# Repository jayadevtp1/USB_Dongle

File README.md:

# USB_Dongle
# PCB Design
started with edgecuts.then place all the components .Then enter into the most time consuming part the pcb rooting.it take me much time.
there occur so many drs connections. then recheck and completed the rooting .All the suffes finished.

# Schematic for the USB_Dongle
started with finding a best microcontroller for this project in online. After some research found out that esp32 is best. 
Then started started cooking. At first findout the essential components and schematic layout of it. Then started cooking schematic diagram in kicad. 
here the schematic that i created.i look ugle that i am not sorted every thing. Then i stoped my work for some time.

**Total time spent: 12h**

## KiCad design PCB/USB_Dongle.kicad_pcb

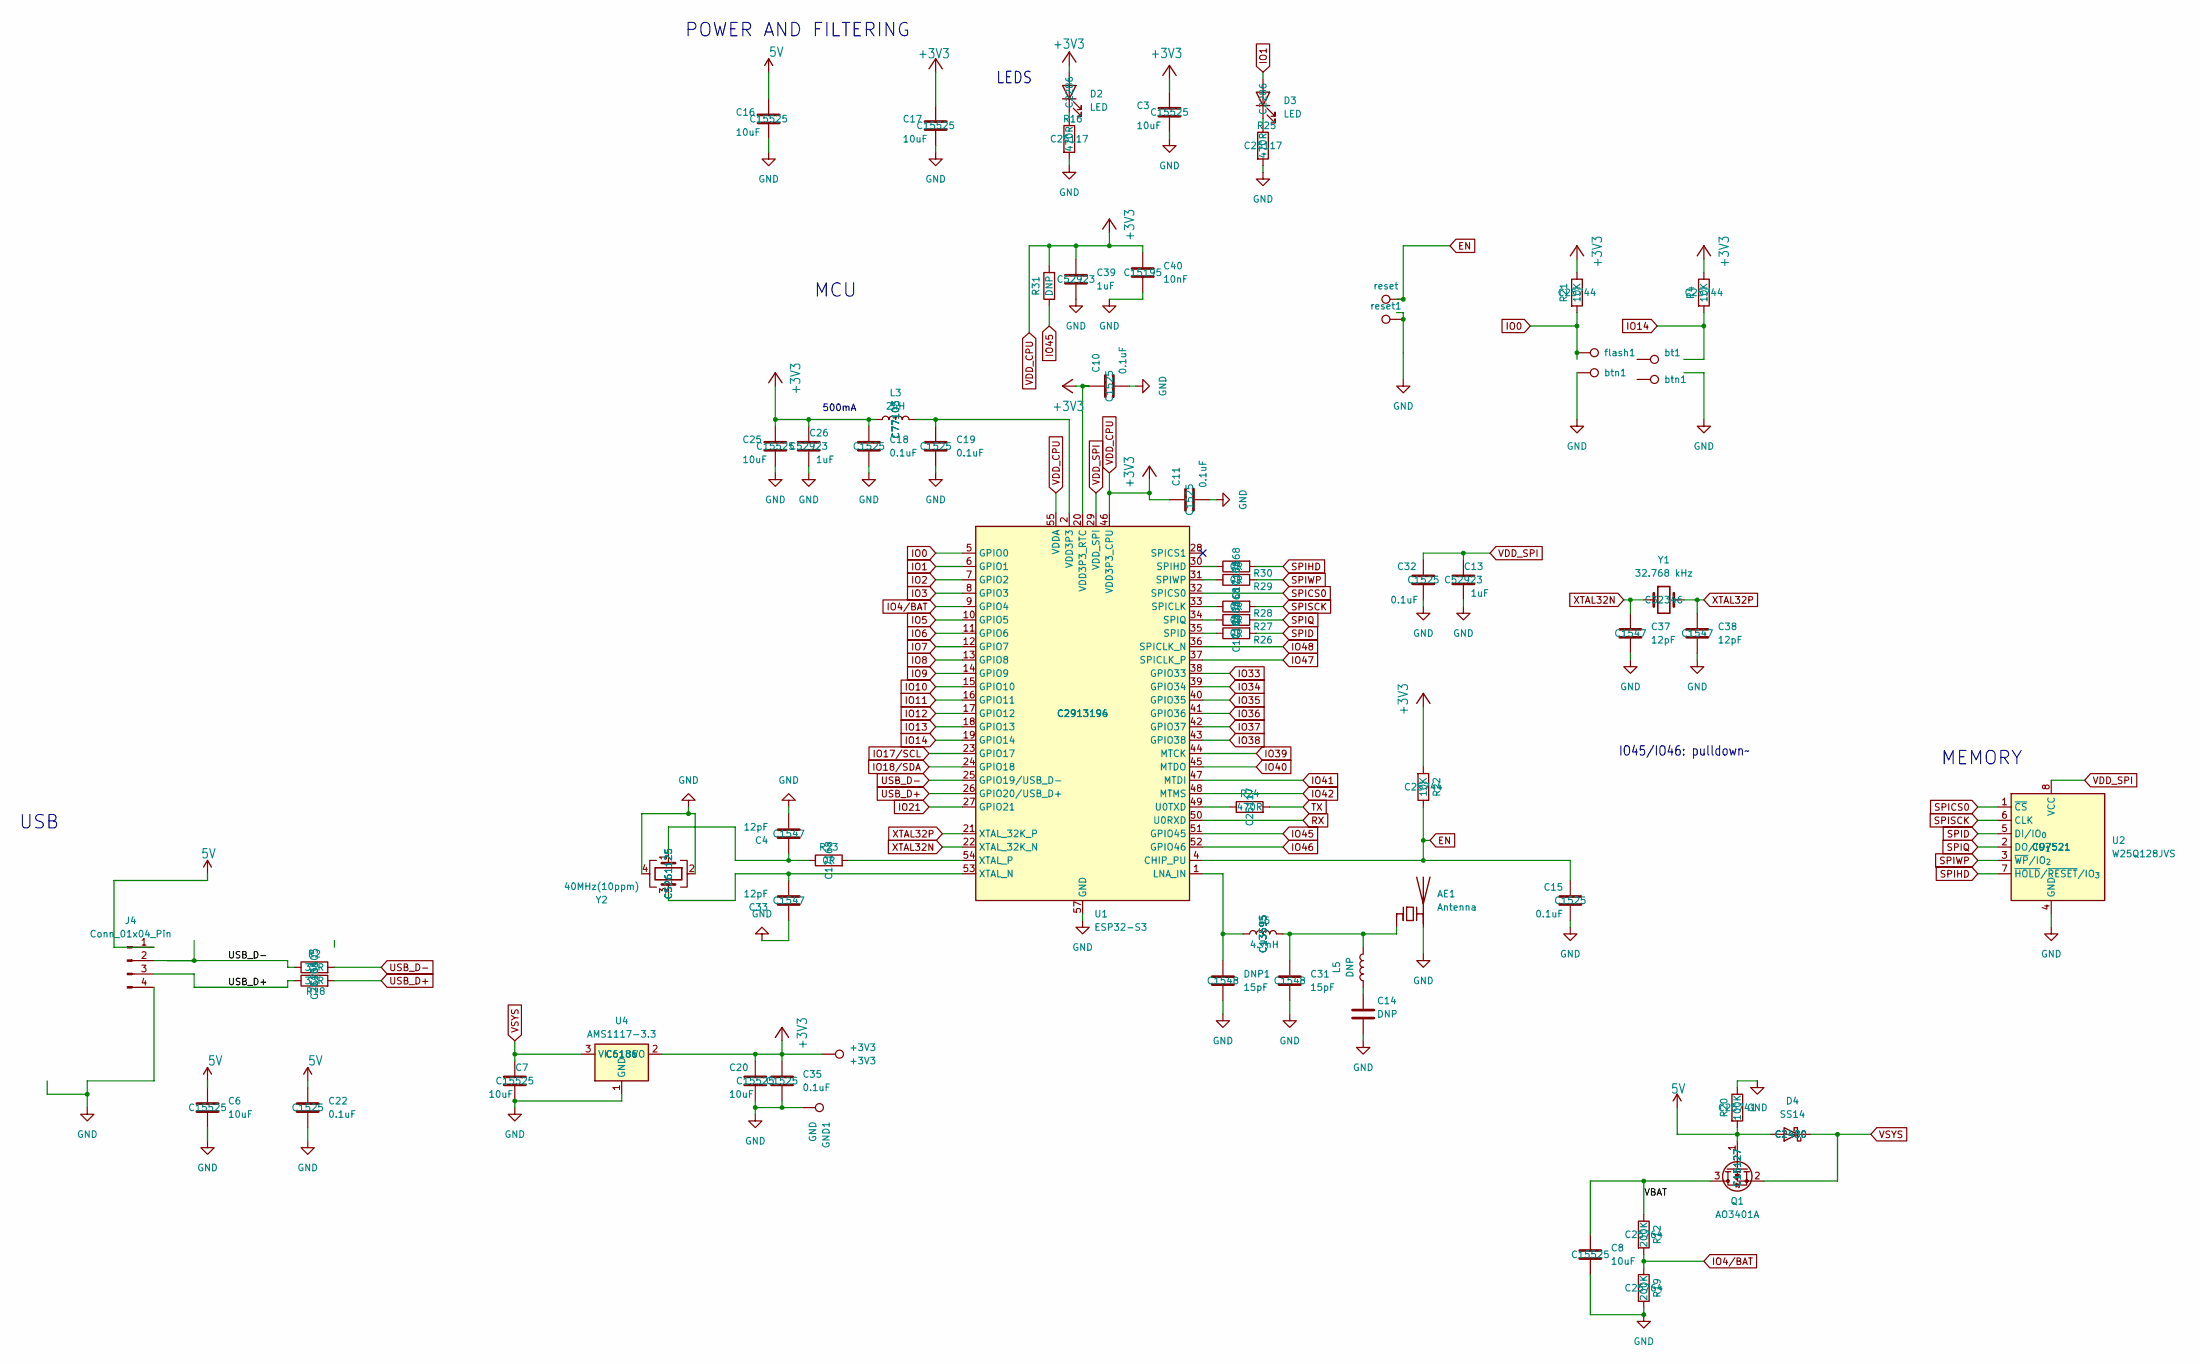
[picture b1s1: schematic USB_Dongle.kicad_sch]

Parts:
+3V1, +3V2: btn1; TestPoint_Pad_D1.0mm
+3V3: +3V3; TestPoint_Pad_D1.0mm
+3V4: reset; TestPoint_Pad_D1.0mm
AE1: Antenna; Texas_SWRA117D_2.4GHz_Left
C3, C6, C7, C8, C16, C17, C20, C25: 10uF; C_0402_1005Metric; MNF PART NUMBER C15525; LCSC C15525
C4, C33, C37, C38: 12pF; C_0402_1005Metric; MNF PART NUMBER C1547; LCSC C1547
C10, C11, C15, C18, C19, C22, C32, C35: 0.1uF; C_0402_1005Metric; MNF PART NUMBER C1525; LCSC C1525
C13, C26, C39: 1uF; C_0402_1005Metric; MNF PART NUMBER C52923; LCSC C52923
C14: DNP; C_0402_1005Metric
C31: 15pF; C_0402_1005Metric; MNF PART NUMBER C1548; LCSC C1548
C40: 10nF; C_0402_1005Metric; MNF PART NUMBER C15195; LCSC C15195
D2, D3: LED; LED_0603_1608Metric; MNF PART NUMBER C2286; LCSC C2286
D4: SS14; D_SMA; MNF PART NUMBER C2480; LCSC C2480
DNP1: 15pF; C_0402_1005Metric; MNF PART NUMBER C1548; LCSC C1548
GND1: GND; TestPoint_Pad_D1.0mm
J4: Conn_01x04_Pin; USB_A_PCB_Edge_receptacle
L3: 2nH; L_0402_1005Metric; MNF PART NUMBER C77103; LCSC C77103
L5: DNP; L_0402_1005Metric
L6: 4.7nH; L_0402_1005Metric; MNF PART NUMBER C13595; LCSC C13595
Q1: AO3401A; SOT-23; MNF PART NUMBER C15127; LCSC C15127
R2, R18: 33R; R_0402_1005Metric; MNF PART NUMBER C25105; LCSC C25105
R4, R21, R22: 10K; R_0402_1005Metric; MNF PART NUMBER C25744; LCSC C25744
R12, R19: 200K; R_0402_1005Metric; MNF PART NUMBER C25764; LCSC C25764
R16, R24, R25: 470R; R_0402_1005Metric; MNF PART NUMBER C25117; LCSC C25117
R20: 100K; R_0402_1005Metric; MNF PART NUMBER C25741; LCSC C25741
R23, R26, R27, R28, R29, R30: 0R; R_0402_1005Metric; MNF PART NUMBER C17168; LCSC C17168
R31: DNP; R_0402_1005Metric
U1: ESP32-S3; QFN-56-1EP_7x7mm_P0.4mm_EP4x4mm; MNF PART NUMBER C2913196; LCSC C2913194
U2: W25Q128JVS; SOIC-8_5.23x5.23mm_P1.27mm; MNF PART NUMBER C97521; LCSC C97521
U4: AMS1117-3.3; SOT-223-3_TabPin2; MNF PART NUMBER C6186; LCSC C6186
Y1: 32.768 kHz; Crystal_SMD_3215-2Pin_3.2x1.5mm; MNF PART NUMBER C32346; LCSC C32346
Y2: 40MHz(10ppm); Crystal_SMD_2520-4Pin_2.5x2.0mm; MNF PART NUMBER C5261125; LCSC C5261125
bt1: +3V3; TestPoint_Pad_D1.0mm
flash1: +3V3; TestPoint_Pad_D1.0mm
reset1: +3V3; TestPoint_Pad_D1.0mm

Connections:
5V: C6.1, C16.1, C22.1, D4.2 (A), J4.1, Q1.1 (G), R20.2
/VBAT: C8.1, Q1.3 (D), R12.1
EN: +3V4.1, C15.1, R22.1, U1.4 (CHIP_PU)
GND: +3V2.1, AE1.2 (PCB_Trace), C3.2, C4.2, C6.2, C7.2, C8.2, C10.2, C11.2, C13.2, C14.2, C15.2, C16.2, C17.2, C18.2, C19.2, C20.2, C22.2, C25.2, C26.2, C31.2, C32.2, C33.1, C35.2, C37.2, C38.2, C39.2, C40.2, DNP1.2, GND1.1, J4.4, R16.2, R19.2, R20.1, R25.2, U1.57 (GND), U2.4 (GND), U4.1 (GND), Y2.2, Y2.4, reset1.1
IO0: R21.2, U1.5 (GPIO0), flash1.1
IO1: D3.2 (A), U1.6 (GPIO1)
IO2: U1.7 (GPIO2)
IO3: U1.8 (GPIO3)
IO4/BAT: R12.2, R19.1, U1.9 (GPIO4)
IO5: U1.10 (GPIO5)
IO6: U1.11 (GPIO6)
IO7: U1.12 (GPIO7)
IO8: U1.13 (GPIO8)
IO9: U1.14 (GPIO9)
IO10: U1.15 (GPIO10)
IO11: U1.16 (GPIO11)
IO12: U1.17 (GPIO12)
IO13: U1.18 (GPIO13)
IO14: R4.2, U1.19 (GPIO14)
IO17/SCL: U1.23 (GPIO17)
IO18/SDA: U1.24 (GPIO18)
IO21: U1.27 (GPIO21)
IO33: U1.38 (GPIO33)
IO34: U1.39 (GPIO34)
IO35: U1.40 (GPIO35)
IO36: U1.41 (GPIO36)
IO37: U1.42 (GPIO37)
IO38: U1.43 (GPIO38)
IO39: U1.44 (MTCK)
IO40: U1.45 (MTDO)
IO41: U1.47 (MTDI)
IO42: U1.48 (MTMS)
IO45: R31.1, U1.51 (GPIO45)
IO46: U1.52 (GPIO46)
IO47: U1.37 (SPICLK_P)
IO48: U1.36 (SPICLK_N)
unnamed: AE1.1 (FEED), C31.1, L5.2, L6.2
unnamed: C4.1, R23.1, Y2.1
unnamed: C14.1, L5.1
unnamed: C19.1, L3.2, U1.2 (VDD3P3), U1.3 (VDD3P3)
unnamed: D2.1 (K), R16.1
unnamed: D3.1 (K), R25.1
unnamed: DNP1.1, L6.1, U1.1 (LNA_IN)
unnamed: R28.1, U1.33 (SPICLK)
unnamed: R26.1, U1.35 (SPID)
unnamed: R30.1, U1.30 (SPIHD)
unnamed: R27.1, U1.34 (SPIQ)
unnamed: R29.1, U1.31 (SPIWP)
unnamed: R24.1, U1.49 (U0TXD)
unnamed: C33.2, U1.53 (XTAL_N), Y2.3
unnamed: R23.2, U1.54 (XTAL_P)
RX: U1.50 (U0RXD)
SPICS0: U1.32 (SPICS0), U2.1 (~CS)
SPID: R26.2, U2.5 (DI/IO_{0})
SPIHD: R30.2, U2.7 (~HOLD/~RESET/IO_{3})
SPIQ: R27.2, U2.2 (DO/IO_{1})
SPISCK: R28.2, U2.6 (CLK)
SPIWP: R29.2, U2.3 (~WP/IO_{2})
TX: R24.2
USB_D+: J4.3, R18.1, R18.2, U1.26 (GPIO20/USB_D+)
USB_D-: J4.2, R2.1, R2.2, U1.25 (GPIO19/USB_D-)
VDD_CPU: +3V3.1, C3.1, C10.1, C11.1, C17.1, C18.1, C20.1, C25.1, C26.1, C35.1, C39.1, C40.1, D2.2 (A), L3.1, R4.1, R21.1, R22.2, R31.2, U1.20 (VDD3P3_RTC), U1.46 (VDD3P3_CPU), U1.55 (VDDA), U1.56 (VDDA), U4.2 (VO)
VDD_SPI: C13.1, C32.1, U1.29 (VDD_SPI), U2.8 (VCC)
VSYS: C7.1, D4.1 (K), Q1.2 (S), U4.3 (VI)
XTAL32N: C37.1, U1.22 (XTAL_32K_N), Y1.1
XTAL32P: C38.1, U1.21 (XTAL_32K_P), Y1.2

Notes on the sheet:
500mA
LEDS
MCU
MEMORY
POWER AND FILTERING
IO45/IO46: pulldown~~{}
USB

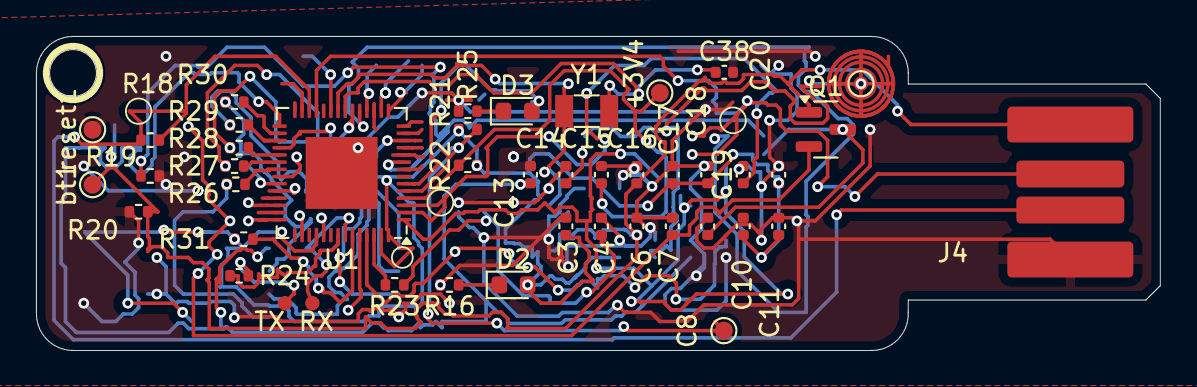
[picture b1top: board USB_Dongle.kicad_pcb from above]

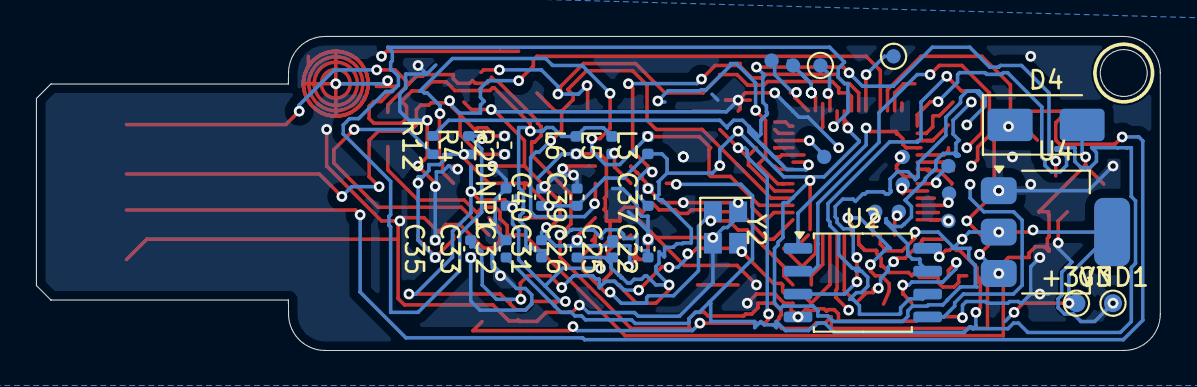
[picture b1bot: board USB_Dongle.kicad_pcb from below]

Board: 2 copper layers, 62.4 x 17.4 mm, 67 parts (25 on the bottom side), 37 nets.

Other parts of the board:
0, 0#2, 0#3: +3V3; TestPoint_Pad_D1.0mm

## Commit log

2025-12-27 Rename USB_Dongle-all-pos.csv to position.csv
